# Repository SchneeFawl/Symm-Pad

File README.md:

# ⌨ Symm-Pad
Macropad named '**Symm Pad**', plan on using this for quick shortcuts which could be used in various applications. <br>
Hardware project (Hackpad) for [Blueprint](https://blueprint.hackclub.com/).

## ⚙ Components to be added
- 6 keys along with backlit LEDs.
- 0.91" OLED display above or beside the keys.
- A rotary encoder knob above the keys, planning to use it as volume control.
- A side LED strip light will also be present on the left and right sides of the pad.

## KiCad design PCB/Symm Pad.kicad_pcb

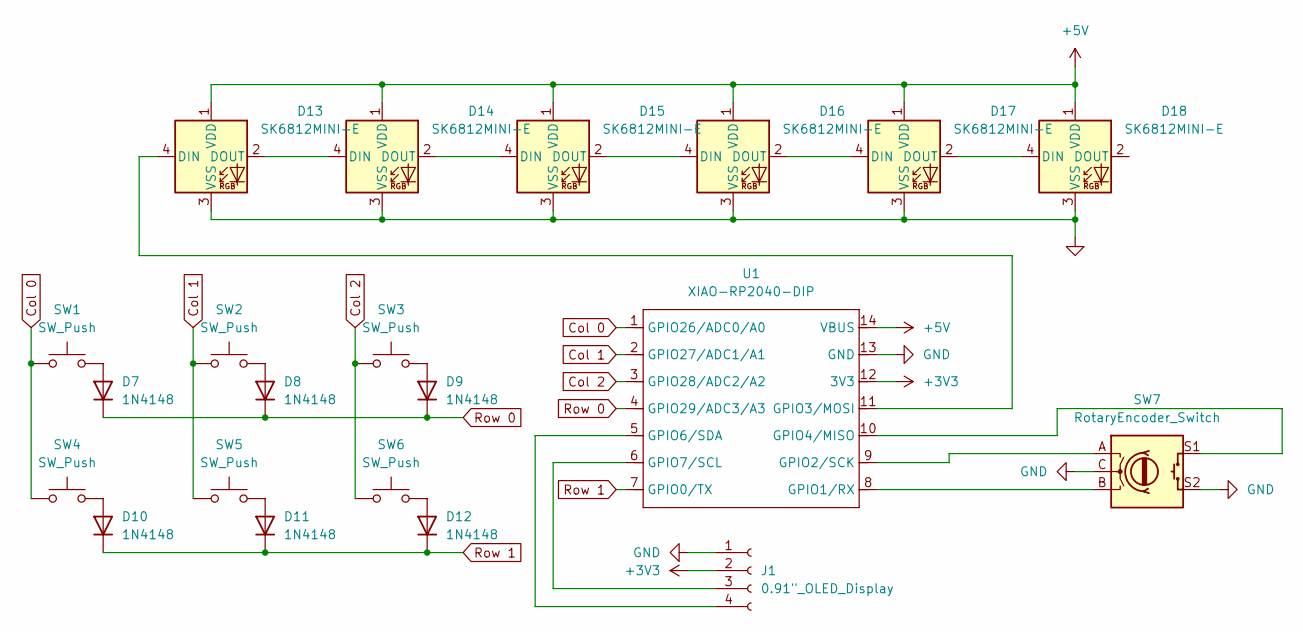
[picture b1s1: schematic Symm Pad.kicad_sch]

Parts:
D7, D8, D9, D10, D11, D12: 1N4148; D_DO-35_SOD27_P7.62mm_Horizontal
D13, D14, D15, D16, D17, D18: SK6812MINI-E; MX_SK6812MINI-E
J1: 0.91"_OLED_Display; SSD1306-0.91-OLED-4pin
SW1, SW2, SW3, SW4, SW5, SW6: SW_Push; SW_Cherry_MX_1.00u_PCB
SW7: RotaryEncoder_Switch; RotaryEncoder_Alps_EC11E-Switch_Vertical_H20mm
U1: XIAO-RP2040-DIP

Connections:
+3V3: J1.2, U1.12 (3V3)
+5V: D13.1 (VDD), D14.1 (VDD), D15.1 (VDD), D16.1 (VDD), D17.1 (VDD), D18.1 (VDD), U1.14 (VBUS)
Col 0: SW1.1, SW4.1, U1.1 (GPIO26/ADC0/A0)
Col 1: SW2.1, SW5.1, U1.2 (GPIO27/ADC1/A1)
Col 2: SW3.1, SW6.1, U1.3 (GPIO28/ADC2/A2)
GND: D13.3 (VSS), D14.3 (VSS), D15.3 (VSS), D16.3 (VSS), D17.3 (VSS), D18.3 (VSS), J1.1, SW7.C, SW7.S2, U1.13 (GND)
unnamed: D7.2 (A), SW1.2
unnamed: D8.2 (A), SW2.2
unnamed: D9.2 (A), SW3.2
unnamed: D10.2 (A), SW4.2
unnamed: D11.2 (A), SW5.2
unnamed: D12.2 (A), SW6.2
unnamed: D13.4 (DIN), U1.11 (GPIO3/MOSI)
unnamed: D13.2 (DOUT), D14.4 (DIN)
unnamed: D14.2 (DOUT), D15.4 (DIN)
unnamed: D15.2 (DOUT), D16.4 (DIN)
unnamed: D16.2 (DOUT), D17.4 (DIN)
unnamed: D17.2 (DOUT), D18.4 (DIN)
unnamed: J1.3, U1.6 (GPIO7/SCL)
unnamed: J1.4, U1.5 (GPIO6/SDA)
unnamed: SW7.B, U1.8 (GPIO1/RX)
unnamed: SW7.A, U1.9 (GPIO2/SCK)
unnamed: SW7.S1, U1.10 (GPIO4/MISO)
Row 0: D7.1 (K), D8.1 (K), D9.1 (K), U1.4 (GPIO29/ADC3/A3)
Row 1: D10.1 (K), D11.1 (K), D12.1 (K), U1.7 (GPIO0/TX)

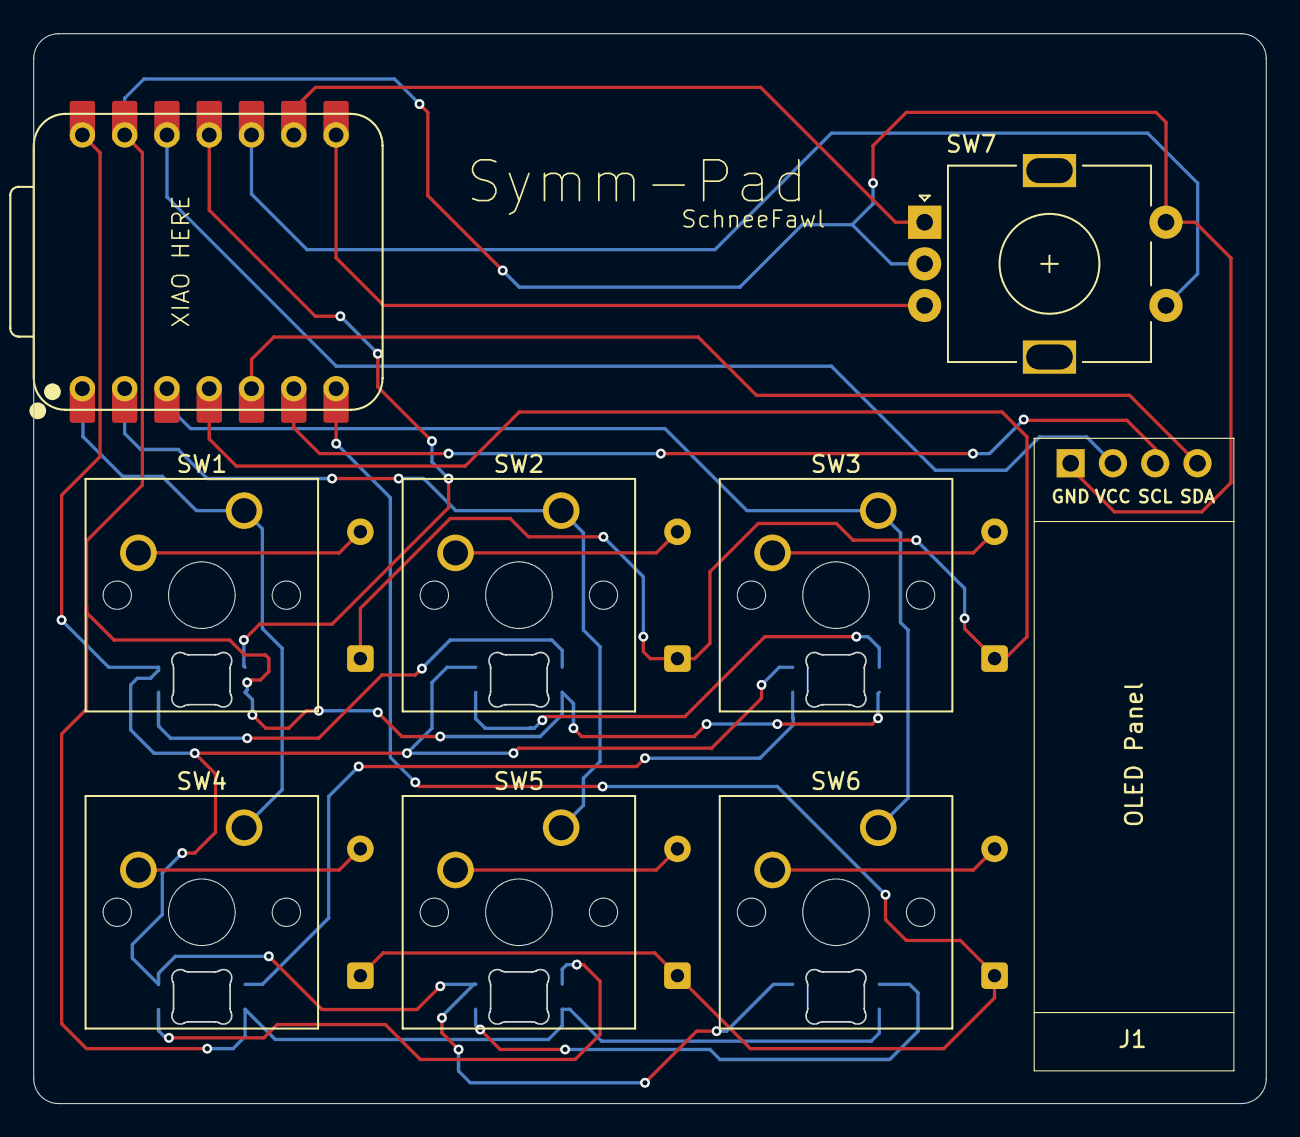
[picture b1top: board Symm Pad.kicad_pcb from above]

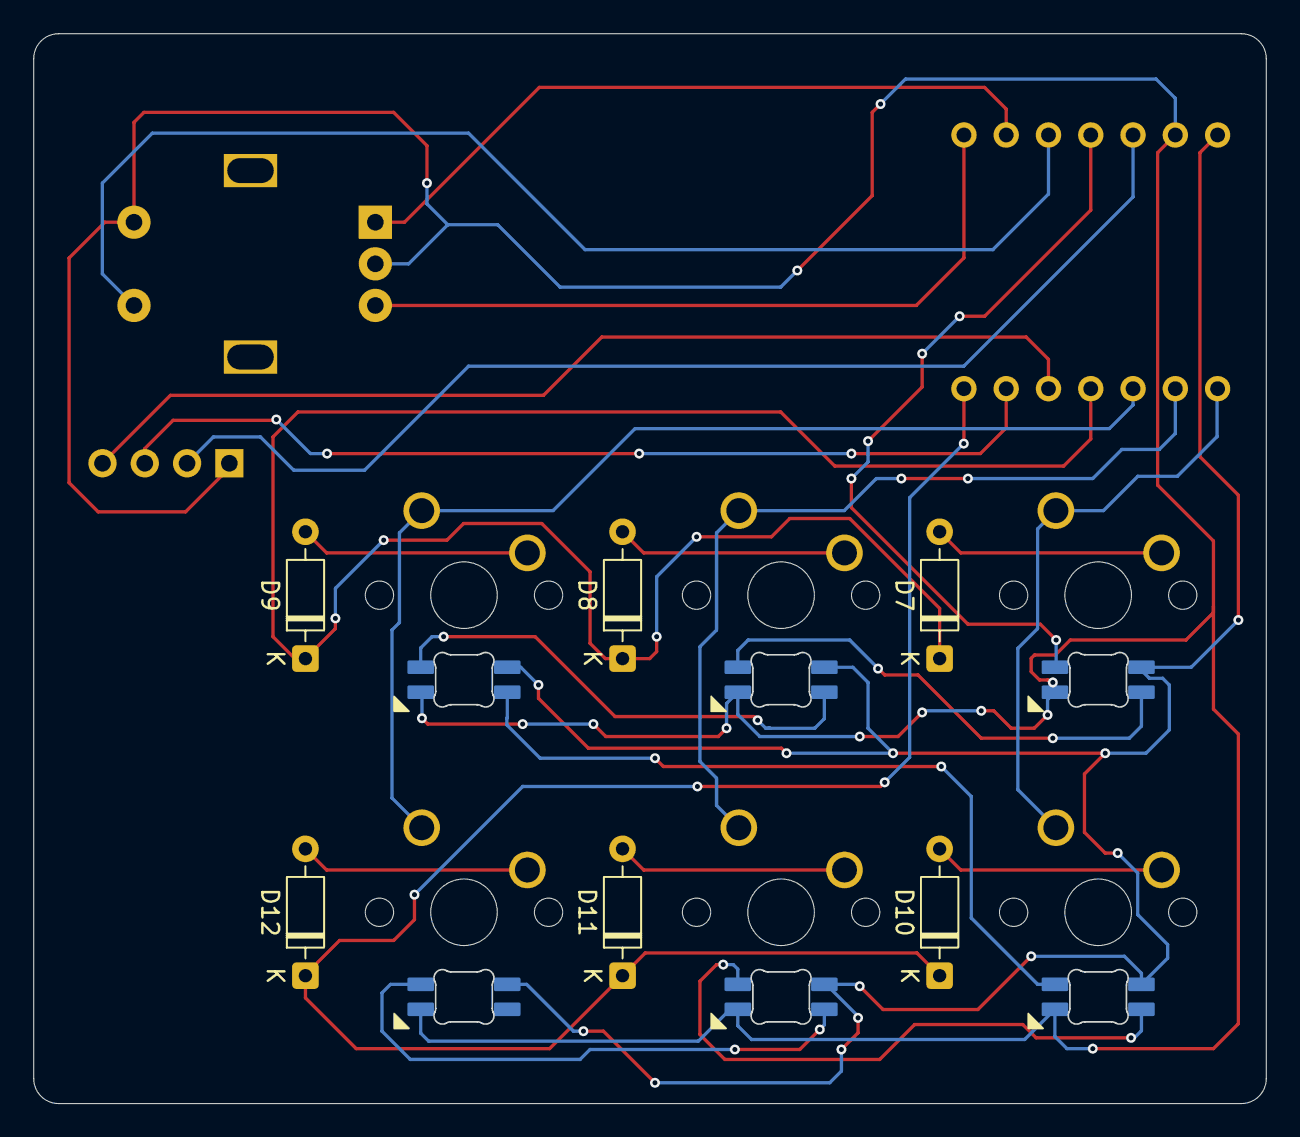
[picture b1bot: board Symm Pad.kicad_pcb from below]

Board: 2 copper layers, 74.0 x 64.2 mm, 21 parts (6 on the bottom side), 25 nets.

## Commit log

2025-12-06 Basic README update
    Added details about the macropad's features.
2025-12-06 Added main components to schematic
    Added basic components like XIAO-RP2040, SW_PUSH (6 units) and SK6812MINI (6 units). Also connected switches the 6 switches to the microcontroller.
2025-12-07 Delete Symm Pad.kicad_pcb
    Files will be organized within a folder in the next change.
2025-12-07 Delete Symm Pad.kicad_pro
    Files will be organized within a folder in the next change.
2025-12-07 Delete Symm Pad.kicad_sch
    Files will be organized within a folder in the next change.
2025-12-07 Major changes and organize into directories
    Added 6 LEDs for backlit, a rotary encoder (EC11) and 0.91" OLED display. Changed the wiring from direct wiring to matrix wiring because I was running short on pins in the microcontroller, needed one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
2025-12-07 Revise README for project details and components
    Formatted and listed components list for clarity.
2025-12-10 Completed the PCB
2025-12-25 Rename Symm Pad.kicad_pro to Symm Pad.kicad_pro
2025-12-25 Cleaned up tracks and vias
2025-12-31 Correct footprint of neopixels
    Earlier the SK6812 MINI footprint was being used which wasn't correct. Now changed to SK6812 MINI-E footprints.
